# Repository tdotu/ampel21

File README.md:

# ampel21
the new version of the BECI-Ampel

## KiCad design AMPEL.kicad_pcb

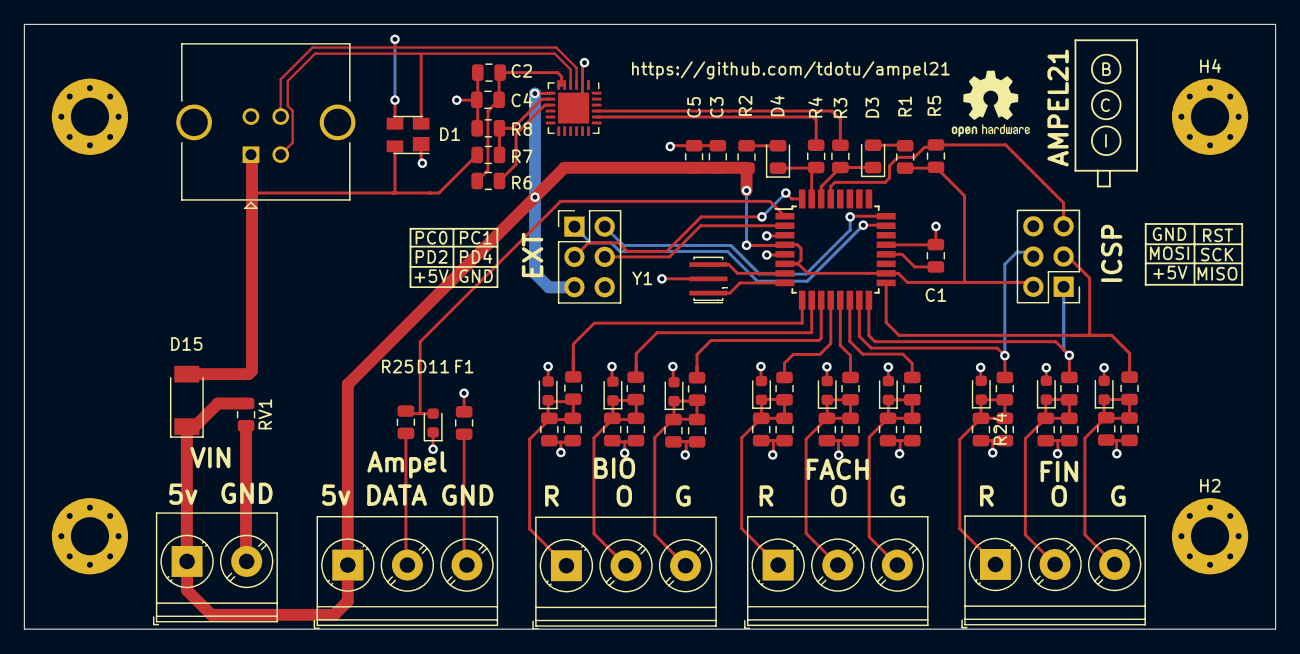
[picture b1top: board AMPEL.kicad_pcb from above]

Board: 2 copper layers, 105.0 x 50.8 mm, 72 parts (0 on the bottom side), 43 nets.

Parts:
C1: 100nF; C_0805_2012Metric
C2, C3: 4.7uF; C_0805_2012Metric
C4, C5: 0.1uF; C_0805_2012Metric
C7, C8, C9, C10, C11, C13, C14, C15, C16: C; C_0805_2012Metric
D1: SP0503BAHT; SOT-143
D3, D4: LED; LED_0805_2012Metric
D5, D6, D7, D8, D9, D10, D11, D12, D13, D14: D_TVS; D_0603_1608Metric
D15: D_Schottky; D_SOD-128
F1: Polyfuse; Fuse_0805_2012Metric
H1, H2, H3, H4: MountingHole_Pad; MountingHole_3.2mm_M3_Pad_Via
J1: USB_B; USB_B_TE_5787834_Vertical
J2, J8: Conn_02x03_Counter_Clockwise; PinHeader_2x03_P2.54mm_Vertical
J3, J4, J5, J7: Screw_Terminal_01x03; TerminalBlock_Phoenix_PT-1,5-3-5.0-H_1x03_P5.00mm_Horizontal
J6: Screw_Terminal_01x02; TerminalBlock_Phoenix_PT-1,5-2-5.0-H_1x02_P5.00mm_Horizontal
R1, R2, R3, R4, R6: 1k; R_0805_2012Metric
R5: 10k; R_0805_2012Metric
R7: 22.1k; R_0805_2012Metric
R8: 47.5k; R_0805_2012Metric
R9, R10, R11, R12, R13, R14, R15, R16, R17, R18, R20, R21, R23, R24, R26, R27, R28, R29: R; R_0805_2012Metric
R25: 330R; R_0805_2012Metric
RV1: Varistor; R_0805_2012Metric
U1: ATmega328P-AU; TQFP-32_7x7mm_P0.8mm
U2: CP2102N-A01-GQFN24; QFN-24-1EP_4x4mm_P0.5mm_EP2.6x2.6mm
Y1: Crystal_GND2; Resonator_SMD_muRata_CSTxExxV-3Pin_3.0x1.1mm_HandSoldering

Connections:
+5V: C3.1, C5.2, D15.1 (K), J2.2, J6.1, J7.1, J8.5, R1.1, R2.1, R5.1, RV1.1, U1.4 (VCC), U1.6 (VCC), U1.18 (AVCC), U2.7 (REGIN)
BIO_GREEN: C8.1, D6.1 (A1), J4.3, R17.2, R20.1
BIO_RED: C13.1, D10.1 (A1), J4.1, R15.2, R26.1
BIO_YELLOW: C10.1, D8.1 (A1), J4.2, R16.2, R23.1
CP2102_VDD: C2.1, C4.1, R6.1, U2.5 (VIO), U2.6 (VDD)
D+: D1.3 (K), J1.3 (D+), U2.3 (D+)
D-: D1.2 (K), J1.2 (D-), U2.4 (D-)
DATA: D11.2 (A2), R25.1, U1.1 (PD3)
FACH_GREEN: C14.1, D12.1 (A1), J5.3, R11.2, R27.1
FACH_RED: C16.1, D14.1 (A1), J5.1, R9.2, R29.1
FACH_YELLOW: C15.1, D13.1 (A1), J5.2, R10.2, R28.1
FIN_GREEN: C7.1, D5.1 (A1), J3.3, R14.2, R18.1
FIN_RED: C11.1, D9.1 (A1), J3.1, R12.2, R24.1
FIN_YELLOW: C9.1, D7.1 (A1), J3.2, R13.2, R21.1
GND: C1.1, C2.2, C3.2, C4.2, C5.1, C7.2, C8.2, C9.2, C10.2, C11.2, C13.2, C14.2, C15.2, C16.2, D1.1 (A), D5.2 (A2), D6.2 (A2), D7.2 (A2), D8.2 (A2), D9.2 (A2), D10.2 (A2), D11.1 (A1), D12.2 (A2), D13.2 (A2), D14.2 (A2), F1.1, H1.1, H2.1, H3.1, H4.1, J1.4 (GND), J1.5 (Shield), J2.6, J6.2, J8.6, R8.2, R18.2, R20.2, R21.2, R23.2, R24.2, R26.2, R27.2, R28.2, R29.2, RV1.2, U1.3 (GND), U1.5 (GND), U1.21 (GND), U2.2 (GND), U2.25 (GND), Y1.2
MISO: J2.1, R13.1, U1.16 (PB4)
MOSI: J2.4, R12.1, U1.15 (PB3)
unnamed: C1.2, U1.20 (AREF)
unnamed: D3.1 (K), R3.1, U1.30 (PD0)
unnamed: D3.2 (A), R1.2
unnamed: D4.1 (K), R4.1, U1.31 (PD1)
unnamed: D4.2 (A), R2.2
unnamed: F1.2, J7.3
unnamed: J7.2, R25.2
unnamed: R6.2, U2.9 (~RSTb)
unnamed: R9.1, U1.12 (PB0)
unnamed: R10.1, U1.13 (PB1)
unnamed: R11.1, U1.14 (PB2)
unnamed: R15.1, U1.9 (PD5)
unnamed: R16.1, U1.10 (PD6)
unnamed: R17.1, U1.11 (PD7)
unnamed: U1.7 (XTAL1/PB6), Y1.3
unnamed: U1.8 (XTAL2/PB7), Y1.1
PC0: J8.1, U1.23 (PC0)
PC1: J8.2, U1.24 (PC1)
PD2: J8.3, U1.32 (PD2)
PD4: J8.4, U1.2 (PD4)
RST: J2.5, R5.2, U1.29 (~RESET~/PC6)
RXD: R4.2, U2.20 (RXD)
SCK: J2.3, R14.1, U1.17 (PB5)
TXD: R3.2, U2.21 (TXD)
VBUS: D1.4 (K), D15.2 (A), J1.1 (VBUS), R7.1
VBUS_DET: R7.2, R8.1, U2.8 (VBUS)

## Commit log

2020-09-18 uploaded hardware
